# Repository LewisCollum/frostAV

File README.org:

Check out [[https://youtu.be/KNiY2aC7Y0c][youtube]], [[https://photos.app.goo.gl/i7FG5oYFuoorvApo9][images]], [[file:org/README.pdf][paper]]

** Getting Started
You do not need a vehicle to get started. As long as you have a
camera/webcam and a computer, you can run this application. This
project uses [[https://python-poetry.org/][Poetry]]. To run the application
#+begin_src bash
  poetry install
  poetry run frostav
#+end_src

Now in your browser, go to =localhost:5000=. If you have a camera
available (at =/dev/video0=) then you should see a livestream of the
camera. You can play around with the annotations provided in the
drop-down. For example, clicking the "signs" annotation will show a
box around detected signs (try holding a "stop" sign phone image in
front of the camera to see). Lane lines can be detected if you have
blue painter's tape held up to the camera (you may need to calibrate
the colors in code due to camera settings).

** I2C Communication
If you are running the application on a board that has i2c (e.g. RPi)
then install =smbus2= and the application will attempt to write JSON
steering and drive values to address =0x32=
#+begin_src bash
  poetry add smbus2
#+end_src

** Figures
[[./org/figure/poster.png]] 

[[./server/README.org.d/figure/FrostAVSystem.png]]

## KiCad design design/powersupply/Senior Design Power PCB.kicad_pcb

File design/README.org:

#+setupFile: ../org/latex_setup.org
#+title: Design
#+author: Lewis Collum

*** Power Supply (Designed by [[https://github.com/ishelly404][Ian Shelly]])
    Designed in KiCad, this power supply is meant to step down a *7.4V
    LiPo battery* to *5V*. It can output up to at least *3.5A*. In
    order to conveniently power USB devices (such as a Raspberry Pi),
    it has a 5V USB output socket.
    
    [[./powersupply/3D Render.PNG]]

*** Frost Schematic (Designed by [[https://github.com/ishelly404][Ian Shelly]])
    The main components on Frost include the Raspberry Pi 4, Arduino,
    OLED status display, and power supply. We also included an
    optional remote fail-safe switch that uses an XBee transmitter and
    receiver.
    
    [[./schematic/schematic.png]]

*** 3D Printed Chassis
    The chassis is a remix of OpenRC on Thingiverse. Here is the most
    recent set of parts printed for mounting the Raspberry Pi,
    powersupply, and camera.

    [[./vehicle/figure/frostAV_newBodyParts_2020-03-26.png]]

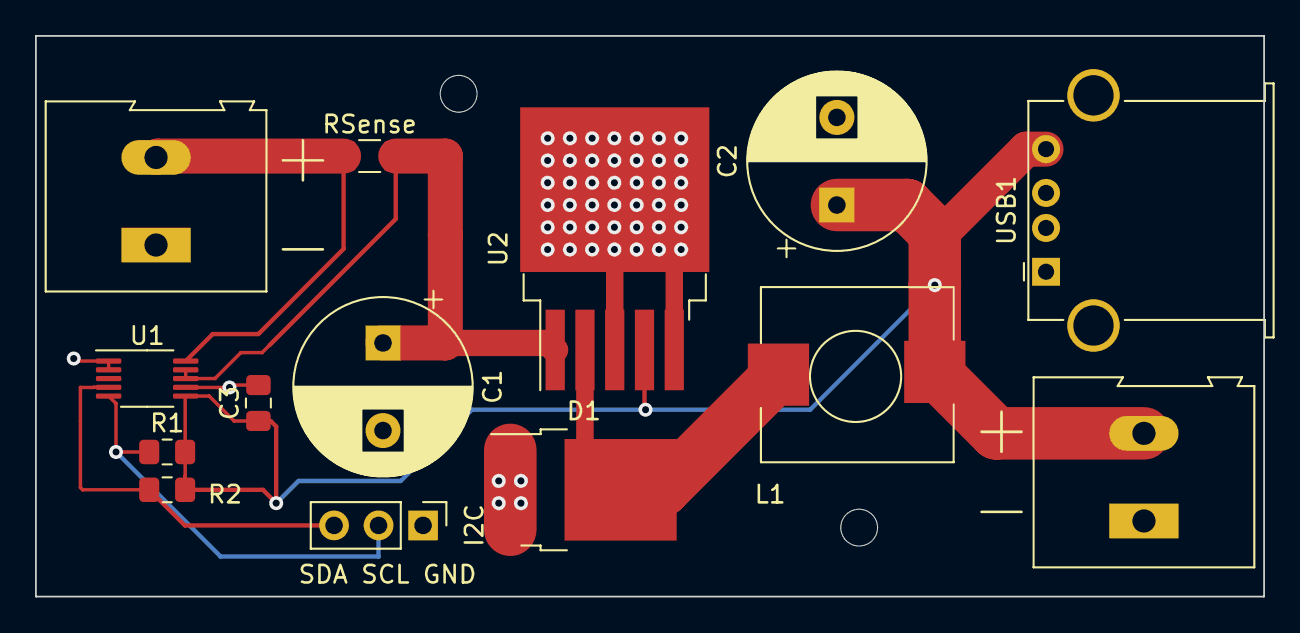
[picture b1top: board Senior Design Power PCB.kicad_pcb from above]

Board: 2 copper layers, 70.1 x 32.0 mm, 13 parts (0 on the bottom side), 5 nets.

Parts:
 : TerminalBlock_Altech_AK300-2_P5.00mm
C1, C2: CP_Radial_D10.0mm_P5.00mm
C3: C_0805_2012Metric_Pad1.15x1.40mm_HandSolder
D1: TO-252-2
I2C: PinHeader_1x03_P2.54mm_Vertical
L1: SRP1038C-330M
R1, R2: R_0805_2012Metric_Pad1.15x1.40mm_HandSolder
RSense: R_1206_3216Metric_Pad1.42x1.75mm_HandSolder
U1: VSSOP-10_3x3mm_P0.5mm
U2: TO-263-5_TabPin3
USB1: USB_A_Stewart_SS-52100-001_Horizontal

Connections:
5V: C2.1, C3.1, L1.2, R1.2, R2.2, U1.6, U2.4, USB1.4
B+: C1.1, RSense.2, U1.8, U1.9, U2.1
B-: .1, C1.2, C2.2, C3.2, D1.1, D1.3, I2C.1, U1.1, U1.2, U1.7, U2.3, U2.5, USB1.1, USB1.5
SCL: I2C.2, R1.1, U1.5
SDA: I2C.3, R2.1, U1.4

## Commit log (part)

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2019-09-03 Added submodules
2019-09-12 Added org/
2019-09-15 Cleaned Project.
2019-09-15 Added requirements.org
2019-09-15 Added functional and constraints
2019-09-15 Added ui.org to requirements.org
2019-09-15 Added some performance requirements
2019-09-15 added to functional requirements
2019-09-15 updated more on perfomance requirements
2019-09-16 updated performance req.
2019-09-16 Set theme jekyll-theme-minimal
2019-09-16 Updated test.org to add some module tests
2019-09-16 added another standard
2019-09-16 Removed title and author.
2019-09-16 README is now the export name for requirements. For github org rendering.
2019-09-16 Export of requirements.org. For GitHub rendering.
2019-09-16 added more constraints
2019-09-16 Created README.
2019-09-16 Layed base for System Requirements Specification.
2019-09-16 Changed heading to title.
2019-09-16 Added table of contents.
2019-09-16 Removed 'Purpose' section.
2019-09-17 Updated requirements. Started adding section CUSTOM_ID.
2019-09-17 Added figures.
2019-09-17 First draft requirements, and test plan done.
2019-09-17 Updated TOC.
2019-09-20 Added AbstractSystem SVG.
2019-09-20 Fixed environment.png size.
2019-09-20 Removed implementation-specific material and reformatted.
2019-09-20 Formatted for GitHub.
2019-09-20 Fixed num:f to num:nil.
2019-09-22 Added Gantt Timeline section.
2019-09-22 Updated export settings.
2019-09-23 Moved AbstractSystem diagram.
2019-09-23 Added Stage 1: Base with Implementation Diagram.
2019-09-23 Added README for FrostAV Development
2019-09-23 Added Developement section links.
2019-09-30 Don't ignore PDFs.
2019-09-30 Finished first draft of stage 1 development specification.
2019-09-30 Updated README org mode options.
2019-10-24 Added Camera to Control diagram.
2019-10-24 Added Control Loop Abstract Diagram
2019-10-31 Added power supply design files
2019-10-31 Added powersupply section
2019-10-31 added buck diagram
2019-11-03 resize buck converter diagram
2019-11-03 added pinout
2019-11-03 added test diagram
2019-11-04 Broadened sweeping range for servo PID experiment.
2019-11-04 Ignore C++ artifacts .elf, .hex, .o
2019-11-04 Adding branch/lane_detection
2019-11-04 Ignore CxxTest artifacts 'runner' and 'runner.cpp'
2019-11-04 Initial Pid. Tests pass with CxxTest and g++17
2019-11-04 Initial Clamp. Tests pass with CxxTest and g++17
2019-11-04 Changed clamping conditionals to ternary operator. Static member function is not working.
2019-11-04 Switched ordering of bounds.
2019-11-04 Servo controlled via USART, with bounds clamping, to avoid an input outside the range of the servo bounds.
2019-11-04 fixed partslist
2019-11-04 Fixed missing test_diagram.
2019-11-04 Fixed image widths for power schematics. Checked spelling for Power sections.
2019-11-05 Fixed static members causing device to not respond, by making them constexpr as well as the contructors they call.
2019-11-05 Ignore dependency files (.d).
2019-11-05 Extracted related code from sweep.cpp into respective files; String.hpp and usart.hpp.
2019-11-05 Implemented PID experimental setup. The current input error is not actual error and needs real feedback error.
2019-11-05 Layed out each section for the steering pid documentation.
2019-11-05 added i2c library
2019-11-05 gitignore latex Minted artifacts.
2019-11-05 Added code snippet background color definition for org-mode code blocks.
2019-11-06 Reduced image sizes. Slight speedup in pdf rendering.
2019-11-06 started atmel studio project
2019-11-06 added files to atmel project
2019-11-06 fixed include problem
2019-11-06 should be functional, simulated but not tested on hardware
2019-11-06 Finished steering servo PID documentation.
2019-11-06 I2C is now responding to master
2019-11-06 recieving i2c message
2019-11-07 i2c working, has control
2019-11-07 Added SyRS to development docs. Fixed speed controller image placement.
2019-11-07 Added symlinks to requirements. Moved latex settings to development.sty. Fixed no code highlighting on 2 code blocks.
2019-11-07 added logic for i2c
2019-11-07 updated com settings
2019-11-07 fixing i2c data processing
2019-11-07 i2c working
2019-11-07 removed unecessary files
2019-11-07 deleted temp
2019-11-07 i2c working, servo fast enough
2019-11-07 working under linux
2019-11-07 Merged laneDetection with docs
2019-11-07 PID working
2019-11-07 working on pid
2019-11-08 Removed stray doc files
2019-11-08 Added live camera script.
2019-11-11 updated makefile atmel studio
2019-11-11 updated linux build
2019-11-11 refactoring
2019-11-19 explicit constructor
2019-11-20 organized
2019-11-20 added html files
2019-11-20 working power supply statistics page
2019-11-20 Started modular makefiles.
2019-11-21 Finished top-level, app/sweep, and common makefiles.
2019-11-21 Restored cxxtest testing for 'common'
2019-11-21 Started multiservo application
2019-11-24 Two sweeping servos with independent position control
2019-11-24 Moved atmel related files to branch 'scrap_atmel'
2019-11-24 Reverted sweep due to overwrite from feature_pid_i2c merge
2019-11-24 Refactored out Cycles namespace for timer cycle calculations. Removed 'clockFrequency' variable from application code since it is defined already as F_CPU.
2019-11-27 Created 'dual_servo' and 'car' singletons to abstract timer register code. Updated app files to use these new abstractions.
2019-11-29 Added 'createNewApp' script.
2019-11-29 Added 'multi_esc_servo' to test sweeping esc and servo.
2019-12-01 updated board layout
2019-12-03 Moved cpp files
2019-12-03 Added new raw video/images with no auto gain
2019-12-03 Removed powersupply 'cache' file
2019-12-03 Added 'handControllingCamera' demo
2019-12-04 Rearranged code in README
2019-12-05 Added Raspberry Pi mount for Arduino FreeCad design
2019-12-05 Added rounded corners
2019-12-05 Fixed PNG exporting bounds
2019-12-05 Added built-in standoffs for Arduino
2019-12-05 Moved I2C_slave to common. Fixed header error
2019-12-08 Use 'car' namespace instead of 'dual_servo'
2019-12-08 Added new TODOs for 'car' namespace
2019-12-08 Added TestString and added constructor for char pointers
2019-12-08 Added 'full' app with a basic state machine for starting and stopping
2019-12-09 Reduce confidence when slope is outside of valid range
2019-12-10 Changed hex newline (0x12) to '\n'
2019-12-10 Fixed int16 truncation for servo range for 'full' app. Added aditional helper functions.
2019-12-11 Created final report folder
2019-12-11 oled
2019-12-12 added overall schematic
2019-12-12 added figures for remote shutoff
2019-12-12 added device tree
2019-12-12 added dto evice tree
2019-12-12 removed junk files
2019-12-12 added to appendix
2019-12-17 Added main README
2019-12-17 Fixed image rotation
2019-12-17 added power supply section
2019-12-17 updated power supply section
2019-12-17 updated requirements specification
2019-12-17 updated pcb photo
2019-12-17 updated power supply schematic
2019-12-17 fixed power supply schematic
2019-12-18 added problems section
2019-12-18 Began radial image processing research. Currently able to unwrap radial images.
2019-12-20 adding to testing
2019-12-20 adding code
2019-12-20 added html
2019-12-20 Added latex default width and code color background
2020-01-28 Added sign detection research section
2020-01-29 Started working on tutorial for Python Keras
2020-01-29 Refactored keras demo
2020-01-29 Added Keras Demo HTML
2020-02-10 Made research font 'roboto'
2020-02-10 Moved stray latex to latex export code block
2020-02-10 Explained reason for download script
2020-02-11 Refactored batch and how batch is viewed.
2020-02-11 Refactored download script, batch singleton, and added class distribution visualization
2020-02-12 Trying to get validation data set for testing
2020-02-13 Added logger to log information about a new training 'run' in a run directory
2020-02-14 Added modelSummary to logging. Fixed 'common' import error by deleting import. Added BatchNormalization layer.
2020-02-14 Made a before and after of batch with preprocessing. Cleaned up README.org heading structure.
2020-02-18 Started Sign Detection
2020-02-18 Added Fall 2019 Poster
2020-02-18 Added poster to home README
2020-02-19 No need for a title
    The poster has a title already
2020-02-19 Running OpenCV YOLO Model on COCO
2020-02-20 Added classifier training run. Added resource link to sign detection.
2020-02-25 Yolo-Lite Model Detecting with 30% maP
2020-02-26 Train using yolov3-tiny-prn
2020-02-26 Added yolov3-tiny-prn config
2020-03-05 Started 04_NodalLaneDetection Basic Node interaction between functional filtering steps for lane detection. Debugging functions (e.g. plotting) can be tied in to the nodal system.
2020-03-11 Added concept Node code for presentation. Also fixed cv2.imshow() not showing all windows. This problem occured because the "static" variable, totalDisplayers, in the Displayer class was not incremen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
2020-03-16 Calibrated tape-line color range in LAB color space instead of HSV. Nodes have built in distribution instead of using a distributor object.
2020-03-26 Made new printable parts - steering linkages - double battery stop - double dean connector clamp - ESC Switch Mount - RPi4 Mount - Front & Back Top Decks (now skinnier to provide easier access to bot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
2020-03-26 Fix "warning: ISO C++ forbids converting a string constant to char*"
2020-03-26 Changed twi to header only
2020-03-26 Refactored. Extracted functions, and changed name.,
2020-03-26 Added two apps. One app for splicing i2c data and controlling the vehicle, and one for testing steering.
2020-03-26 Changed directory name from vehicle_interface_controller to vehicleInterfaceController. I'm liking camelCase more
2020-03-26 Added link to google photos
2020-03-27 Created a setup script for the server, and documented installing and starting the server.
2020-03-29 Improved UI. Gave Node state output. Refactored the lane detection system. Simplified threading for opencv camera.
2020-03-29 Fixed GUnicorn error unable to open camera. Changed video "source" from '0' OR 'sys.argv[1]' to only '0' (indicating /dev/video0).
    The "source" of the camera, before, was sys.argv[1] if sys.srgv[1]
    existed, otherwise it was /dev/video0. This is fine when prototyping
    with Flask, since we typically do not include a parameter for
    sys.argv[1] (when running 'python __init__.py <could put source
    here>'). However, gunicorn DOES have command-line arguments and
    sys.argv[1] is NOT a video source. For this reason, it couln't read
2020-04-03 Server Overview (Nginx) removed talk about reverse proxy
2020-04-03 Changed Overview heading depth
2020-04-04 Added Frame Modifiers.
    - Added ROI parameters for constraining the bouding region.
    - Added 'if <list> is not None' in a few places to fix 'None is not iterable' error
    - Attempted to use CLAHE (not working any better for LAB color space)
    - Added Cross Track Error calculator
2020-04-09 Signs detected @ 1 Frame Per 5 Seconds
2020-04-10 Logging FPS of sign detection.
2020-04-22 Lane Error, Sign detection, and basic steering & sign reaction.
2020-04-22 Removed redundant target-file name
2020-04-22 Added Power Supply Description & Render Image
2020-04-22 Added top-level schematic description & image
2020-04-22 Replaced schematic pdf with png
2020-04-22 Added March 2020 3d printables
2020-04-22 Added 3D printed chassis section
2020-04-23 Added index for frostserver
2020-05-07 Added youtube video link
2020-05-12 Added title
2020-05-13 Started Sign README
2020-05-13 Started final report combination
2020-05-13 Added missing READMEs and blocks
2020-05-13 Added VIC README pdf
2020-05-13 Finished paper
2020-05-19 Added action panel
2020-05-19 Create LICENSE
2020-05-19 button categories deduced from models
2020-07-12 Renamed directories
2020-07-12 Added ReadTheOrg rendering and fixed hardcoded server service paths.
2020-07-12 Fixed path
2020-08-26 vehicleModel automatically uses a stub VehicleInterfaceController if smbus2 isn't installed
2020-08-29 Created top-level model in 'model' directory (__init__.py)
2020-10-14 Extracted frost logic from server (flask) code
2020-11-16 Cleaned javascript button panel creation
2020-11-16 Cleaned server entry-point formatting
2022-06-01 Fixed broken doc figure links for org/README.org
2022-06-01 Updated LICENSE to 2022
2022-06-01 Use Poetry to handle Python dependencies, environment, running
